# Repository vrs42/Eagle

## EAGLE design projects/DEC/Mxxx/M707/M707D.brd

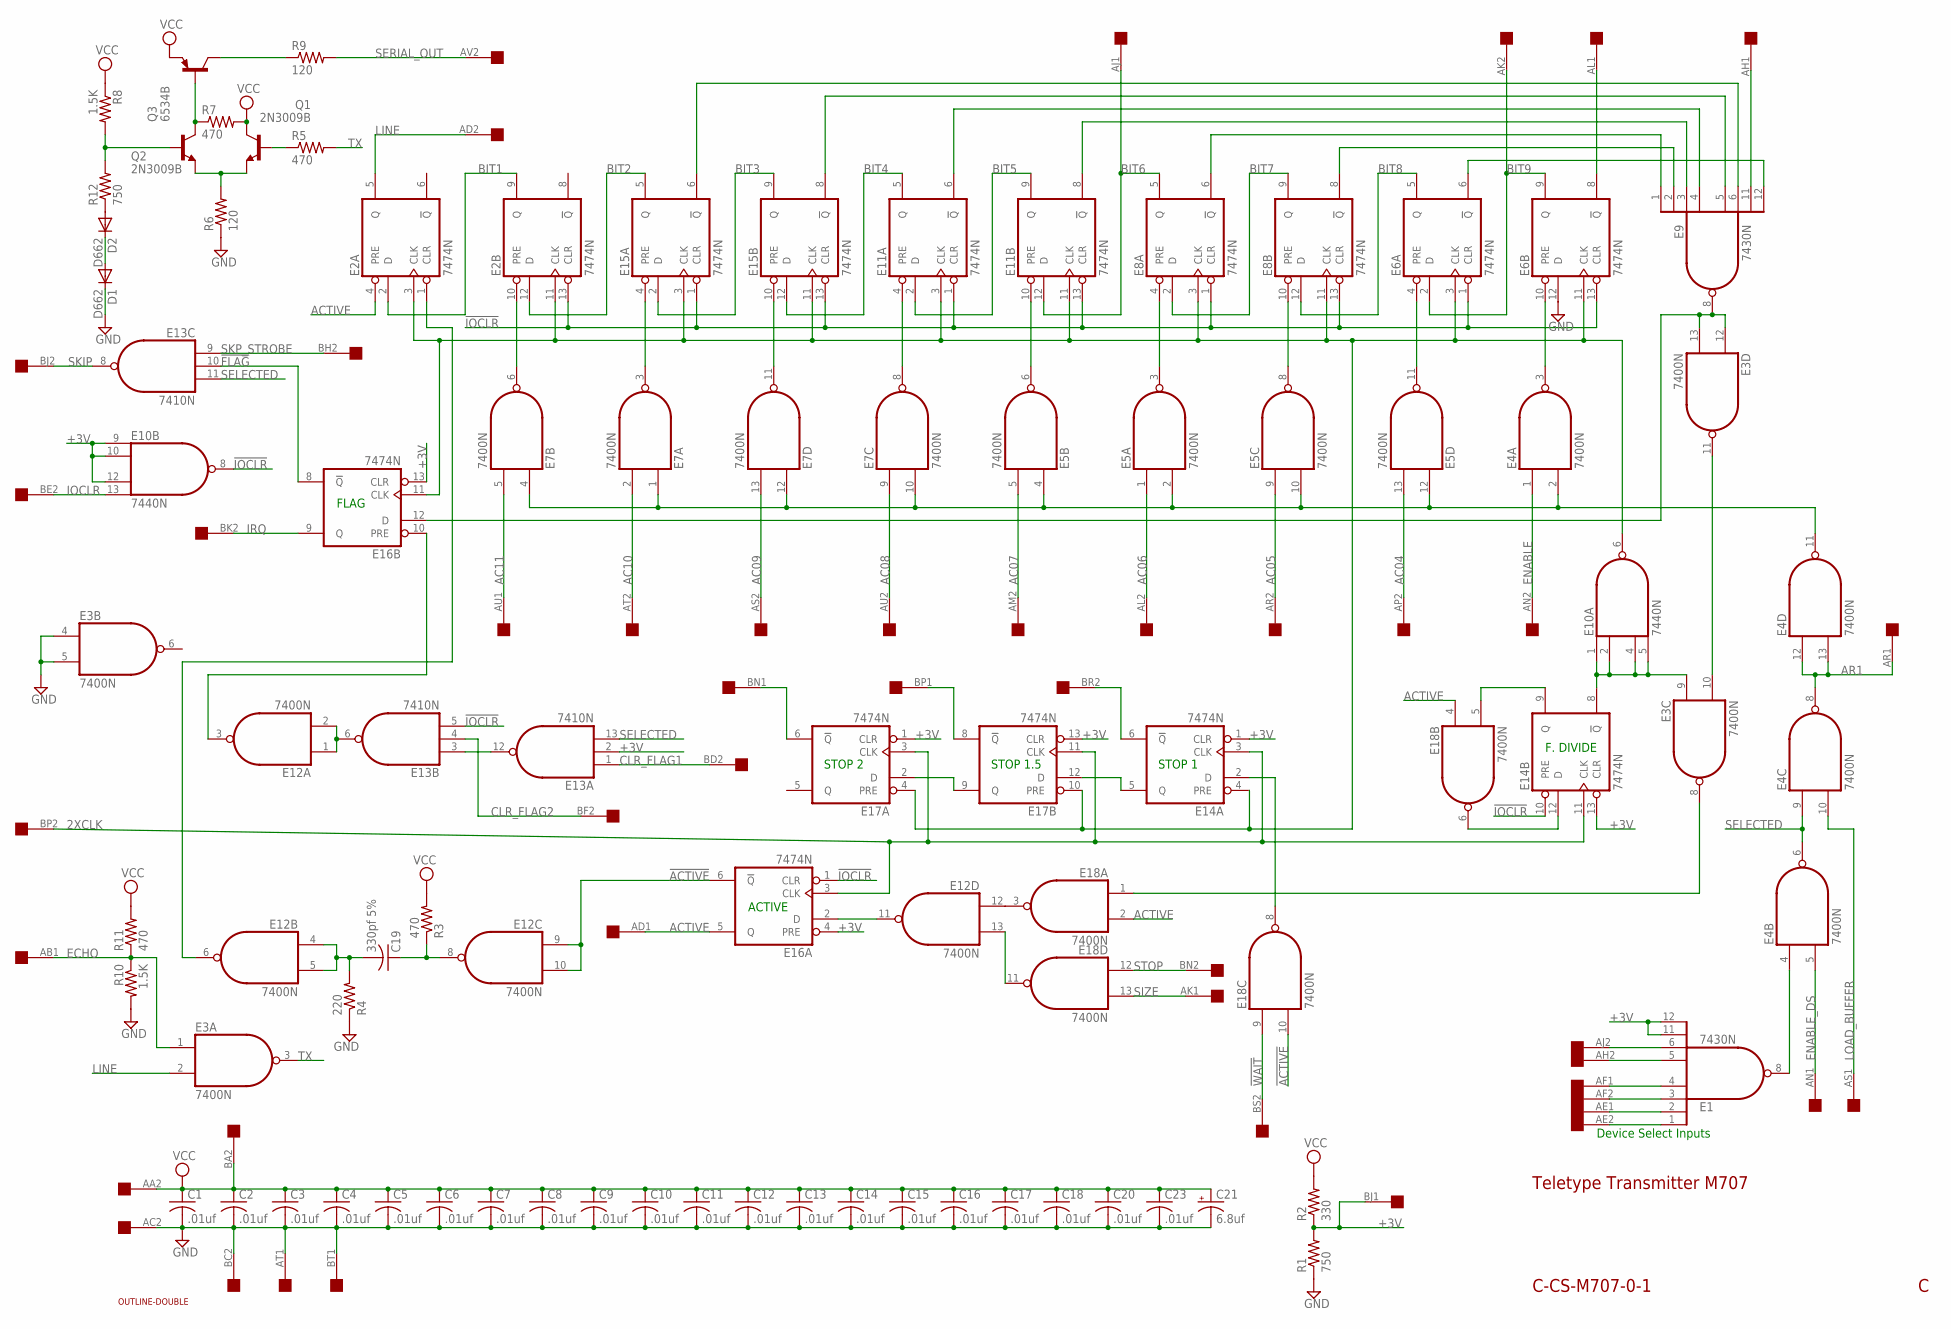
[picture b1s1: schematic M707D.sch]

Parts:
C1, C2, C3, C4, C5, C6, C7, C8, C9, C10, C11, C12, C13, C14, C15, C16, C17, C18, C20, C23: .01uf; C050-025X075
C19: 330pf 5%; C075-032X103
C21: 6.8uf; E15-5
D1, D2: D662; DO35-10
E1, E9: 7430N; DIL14
E2, E6, E8, E11, E14, E15, E16, E17: 7474N; DIL14
E3, E4, E5, E7, E12, E18: 7400N; DIL14
E10: 7440N; DIL14
E13: 7410N; DIL14
Q1, Q2: 2N3009B; TO39
Q3: 6534B; TO39
R1, R12: 750; 0207/10
R2: 330; 0207/10
R3, R5, R7, R11: 470; 0207/10
R4: 220; 0207/10
R6, R9: 120; 0207/10
R8, R10: 1.5K; 0207/10
U$1: OUTLINE-DOUBLE; DOUBLE
U$2: DOUBLE; EDGE-CON4

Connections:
2XCLK: E14.3 (CLK), E14.11 (CLK), E16.3 (CLK), E17.3 (CLK), E17.11 (CLK), U$2.BP2
!ACTIVE: E12.9 (I0), E12.10 (I1), E16.6 (!Q), E18.10 (I1)
!FLAG: E13.10 (I1), E16.8 (!Q)
!IOCLR: E2.13 (CLR), E6.1 (CLR), E6.13 (CLR), E8.1 (CLR), E8.13 (CLR), E10.8 (O), E11.1 (CLR), E11.13 (CLR), E13.5 (I2), E14.10 (PRE), E15.1 (CLR), E15.13 (CLR), E16.1 (CLR)
!WAIT: E18.9 (I0), U$2.BS2
+3V: E1.11 (I6), E1.12 (I7), E10.9 (I0), E10.10 (I1), E10.12 (I2), E13.2 (I1), E14.1 (CLR), E14.13 (CLR), E16.4 (PRE), E16.13 (CLR), E17.1 (CLR), E17.13 (CLR), R1.2, R2.1, U$2.BJ1
AC04: E5.13 (I1), U$2.AP2
AC05: E5.9 (I0), U$2.AR2
AC06: E5.1 (I0), U$2.AL2
AC07: E5.5 (I1), U$2.AM2
AC08: E7.9 (I0), U$2.AU2
AC09: E7.13 (I1), U$2.AS2
AC10: E7.2 (I1), U$2.AT2
AC11: E7.5 (I1), U$2.AU1
ACTIVE: E2.4 (PRE), E16.5 (Q), E18.2 (I1), E18.4 (I0), U$2.AD1
AE1: E1.2 (I1), U$2.AE1
AF1: E1.4 (I3), U$2.AF1
AH1: E9.11 (I6), U$2.AH1
AL1: E6.8 (!Q), U$2.AL1
AR1: E4.8 (O), E4.12 (I0), E4.13 (I1), U$2.AR1
BIT1: E2.2 (D), E2.9 (Q)
BIT2: E2.12 (D), E15.5 (Q)
BIT3: E15.2 (D), E15.9 (Q)
BIT4: E11.5 (Q), E15.12 (D)
BIT5: E11.2 (D), E11.9 (Q)
BIT6: E8.5 (Q), E11.12 (D), U$2.AJ1
BIT7: E8.2 (D), E8.9 (Q)
BIT8: E6.5 (Q), E8.12 (D)
BIT9: E6.2 (D), E6.9 (Q), U$2.AK2
BN1: E17.6 (!Q), U$2.BN1
BP1: E17.8 (!Q), U$2.BP1
CLR_FLAG1: E13.1 (I0), U$2.BD2
CLR_FLAG2: E13.4 (I1), U$2.BF2
ECHO: E3.1 (I0), R10.1, R11.1, U$2.AB1
ENABLE: E4.1 (I0), U$2.AN2
ENABLE_DS: E4.5 (I1), U$2.AN1
GND: C1.2, C2.2, C3.2, C4.2, C5.2, C6.2, C7.2, C8.2, C9.2, C10.2, C11.2, C12.2, C13.2, C14.2, C15.2, C16.2, C17.2, C18.2, C20.2, C21.-, C23.2, D1.C, E1.7 (GND), E2.7 (GND), E3.4 (I0), E3.5 (I1), E3.7 (GND), E4.7 (GND), E5.7 (GND), E6.7 (GND), E6.12 (D), E7.7 (GND), E8.7 (GND), E9.7 (GND), E10.7 (GND), E11.7 (GND), E12.7 (GND), E13.7 (GND), E14.7 (GND), E15.7 (GND), E16.7 (GND), E17.7 (GND), E18.7 (GND), R1.1, R4.1, R6.1, R10.2, U$2.AC2, U$2.AT1, U$2.BC2, U$2.BT1
IOCLR: E10.13 (I3), U$2.BE2
IRQ: E16.9 (Q), U$2.BK2
LINE: E2.5 (Q), E3.2 (I1), U$2.AD2
LOAD_BUFFER: E4.10 (I1), U$2.AS1
unnamed: C19.1, E12.8 (O), R3.1
unnamed: C19.2, E12.4 (I0), E12.5 (I1), R4.2
unnamed: E5.11 (O), E6.4 (PRE)
unnamed: E2.1 (CLR), E12.6 (O)
unnamed: E2.3 (CLK), E2.11 (CLK), E6.3 (CLK), E6.11 (CLK), E8.3 (CLK), E8.11 (CLK), E10.6 (O), E11.3 (CLK), E11.11 (CLK), E14.4 (PRE), E15.3 (CLK), E15.11 (CLK), E16.11 (CLK), E17.4 (PRE), E17.10 (PRE)
unnamed: E3.12 (I0), E3.13 (I1), E9.8 (O), E16.12 (D)
unnamed: E6.6 (!Q), E9.12 (I7)
unnamed: Q3.3 (C), R9.1
unnamed: E1.8 (O), E4.4 (I0)
unnamed: E12.12 (I0), E18.3 (O)
unnamed: E14.12 (D), E18.6 (O)
unnamed: E1.6 (I5), U$2.AJ2
unnamed: E1.5 (I4), U$2.AH2
unnamed: E1.3 (I2), U$2.AF2
unnamed: E14.9 (Q), E18.5 (I1)
unnamed: E1.1 (I0), U$2.AE2
unnamed: E9.6 (I5), E15.6 (!Q)
unnamed: E4.2 (I1), E4.11 (O), E5.2 (I1), E5.4 (I0), E5.10 (I1), E5.12 (I0), E7.1 (I0), E7.4 (I0), E7.10 (I1), E7.12 (I0)
unnamed: E4.3 (O), E6.10 (PRE)
unnamed: D1.A, D2.C
unnamed: D2.A, R12.1
unnamed: Q1.2 (B), R5.1
unnamed: Q2.3 (C), Q3.2 (B), R7.1
unnamed: Q1.1 (E), Q2.1 (E), R6.2
unnamed: E12.11 (O), E16.2 (D)
unnamed: Q2.2 (B), R8.2, R12.2
unnamed: E12.1 (I0), E12.2 (I1), E13.6 (O)
unnamed: E9.5 (I4), E15.8 (!Q)
unnamed: E7.3 (O), E15.4 (PRE)
unnamed: E3.9 (I0), E10.1 (I0), E10.2 (I1), E10.4 (I2), E10.5 (I3), E14.8 (!Q)
unnamed: E3.8 (O), E18.1 (I0)
unnamed: E7.8 (O), E11.4 (PRE)
unnamed: E9.4 (I3), E11.6 (!Q)
unnamed: E7.11 (O), E15.10 (PRE)
unnamed: E5.3 (O), E8.4 (PRE)
unnamed: E2.10 (PRE), E7.6 (O)
unnamed: E12.13 (I1), E18.11 (O)
unnamed: E14.6 (!Q), U$2.BR2
unnamed: E13.3 (I0), E13.12 (O)
unnamed: E17.2 (D), E17.9 (Q)
unnamed: E8.6 (!Q), E9.1 (I0)
unnamed: E8.8 (!Q), E9.2 (I1)
unnamed: E9.3 (I2), E11.8 (!Q)
unnamed: E14.2 (D), E18.8 (O)
unnamed: E14.5 (Q), E17.12 (D)
unnamed: E12.3 (O), E16.10 (PRE)
unnamed: E5.8 (O), E8.10 (PRE)
unnamed: E5.6 (O), E11.10 (PRE)
unnamed: E3.10 (I1), E3.11 (O)
SELECTED: E4.6 (O), E4.9 (I0), E13.11 (I2), E13.13 (I2)
SERIAL_OUT: R9.2, U$2.AV2
SIZE: E18.13 (I1), U$2.AK1
SKIP: E13.8 (O), U$2.BJ2
SKP_STROBE: E13.9 (I0), U$2.BH2
STOP: E18.12 (I0), U$2.BN2
TX: E3.3 (O), R5.2
VCC: C1.1, C2.1, C3.1, C4.1, C5.1, C6.1, C7.1, C8.1, C9.1, C10.1, C11.1, C12.1, C13.1, C14.1, C15.1, C16.1, C17.1, C18.1, C20.1, C21.+, C23.1, E1.14 (VCC), E2.14 (VCC), E3.14 (VCC), E4.14 (VCC), E5.14 (VCC), E6.14 (VCC), E7.14 (VCC), E8.14 (VCC), E9.14 (VCC), E10.14 (VCC), E11.14 (VCC), E12.14 (VCC), E13.14 (VCC), E14.14 (VCC), E15.14 (VCC), E16.14 (VCC), E17.14 (VCC), E18.14 (VCC), Q1.3 (C), Q3.1 (E), R2.2, R3.2, R7.2, R8.1, R11.2, U$2.AA2, U$2.BA2

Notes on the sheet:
C-CS-M707-0-1
Teletype Transmitter M707
Device Select Inputs
F. DIVIDE
FLAG
ACTIVE
STOP 2
STOP 1.5
STOP 1

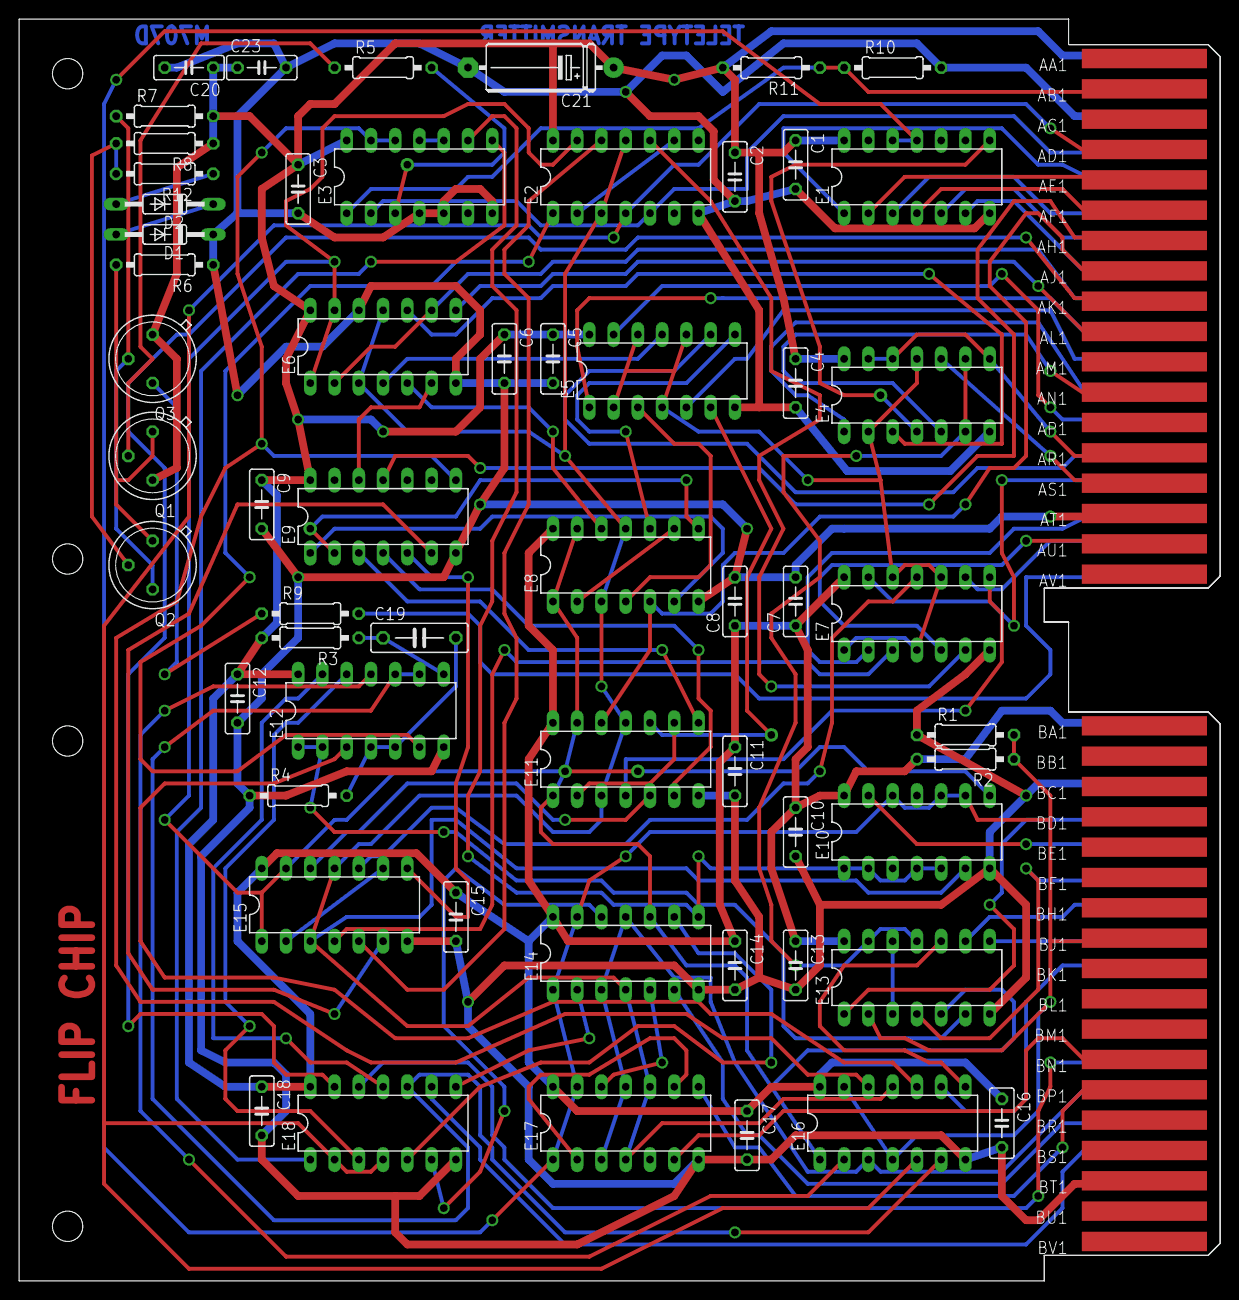
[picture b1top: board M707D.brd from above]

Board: 2 copper layers, 125.7 x 132.1 mm, 59 parts (0 on the bottom side), 98 nets.

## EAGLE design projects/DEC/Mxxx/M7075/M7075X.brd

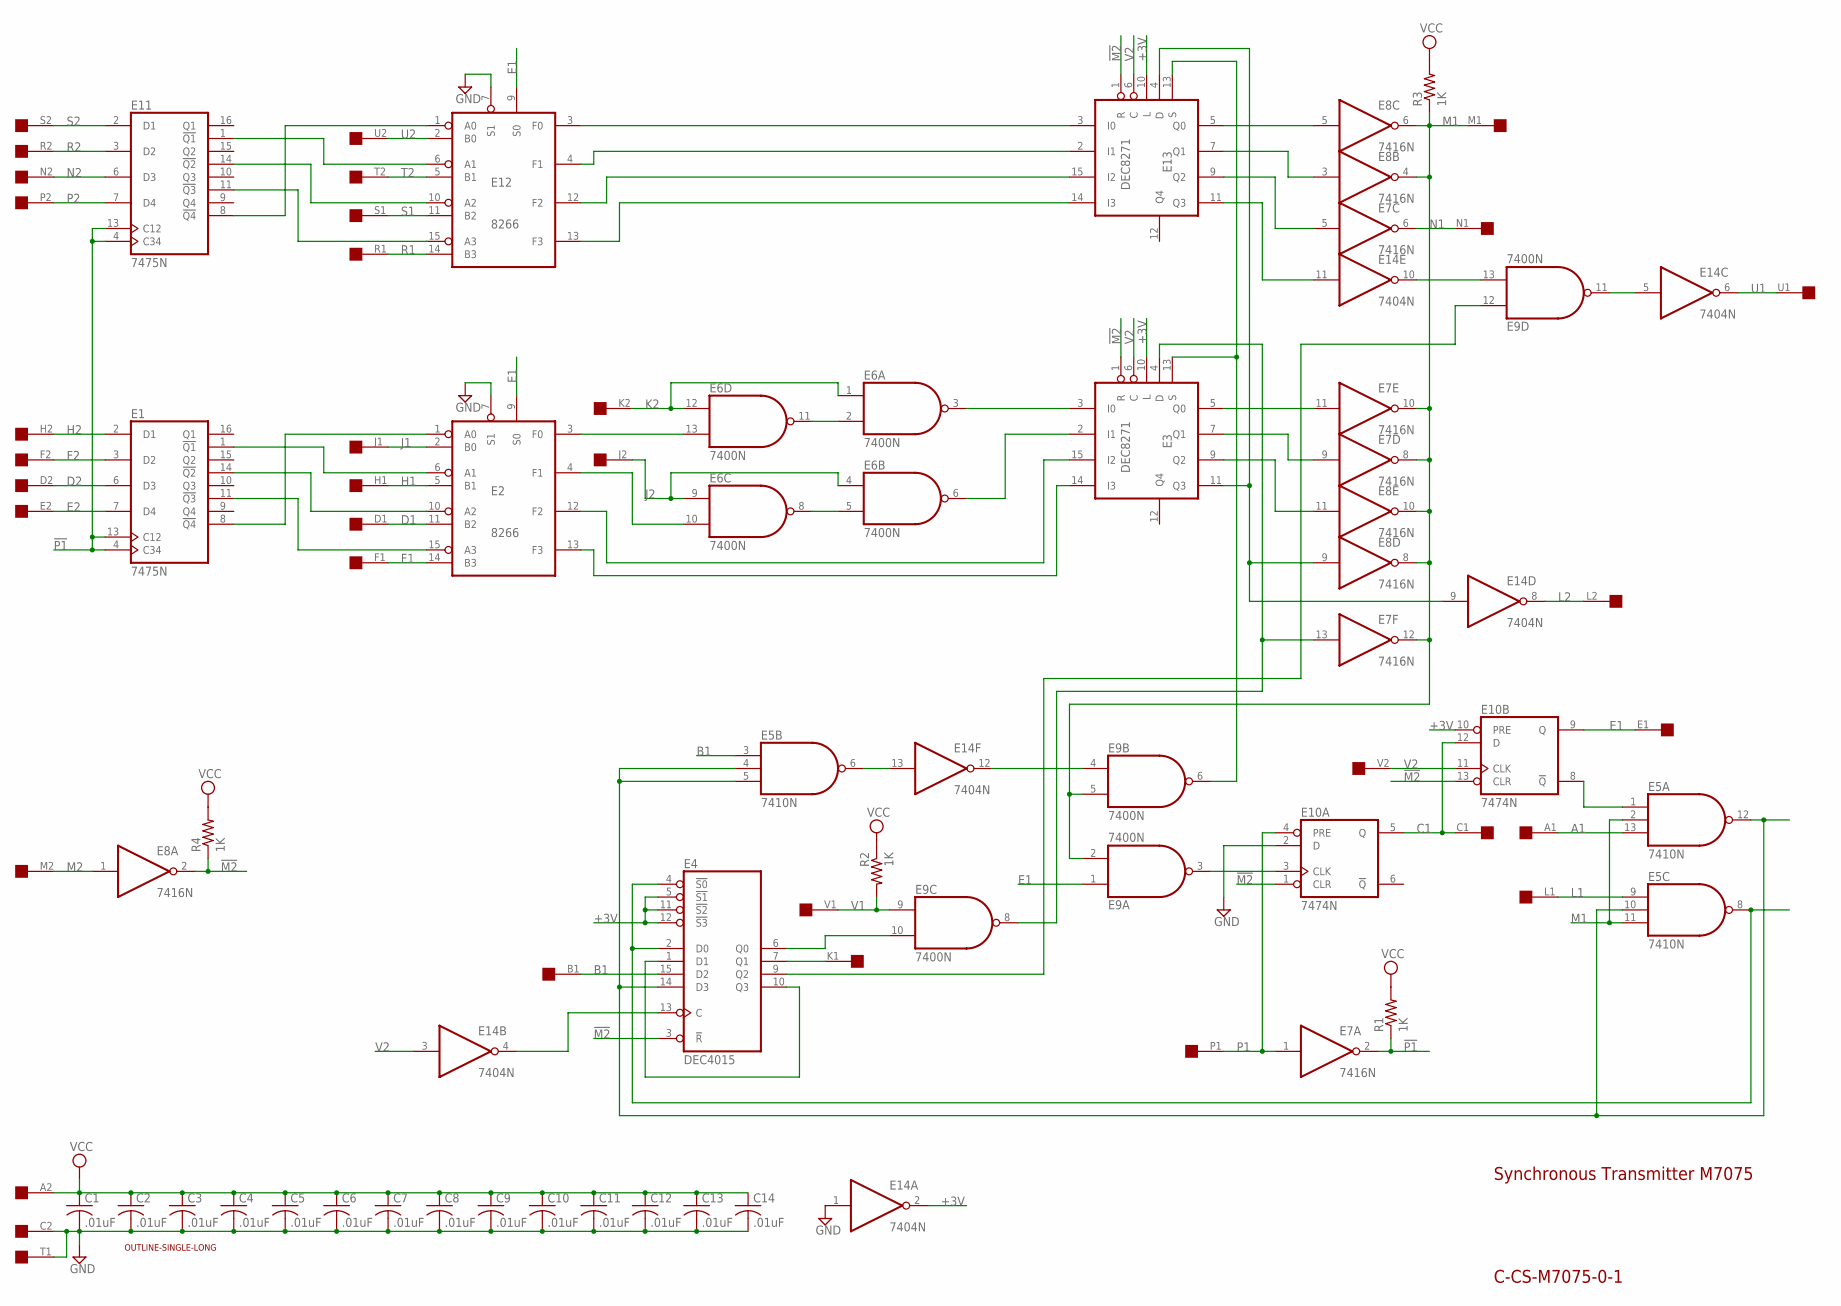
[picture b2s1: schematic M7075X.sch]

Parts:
C1, C2, C3, C4, C5, C6, C7, C8, C9, C10, C11, C12, C13, C14: .01uF; C050-025X075
E1, E11: 7475N; DIL16
E2, E12: 8266; DIL16
E3, E13: DEC8271; DIL16
E4: DEC4015; DIL16
E5: 7410N; DIL14
E6, E9: 7400N; DIL14
E7, E8: 7416N; DIL14
E10: 7474N; DIL14
E14: 7404N; DIL14
R1, R2, R3, R4: 1K; 0207/10
U$1: OUTLINE-SINGLE-LONG; SINGLE-LONG
U$2: SINGLE; EDGE-CON2

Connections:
!M2: E3.1 (R), E4.3 (!R), E8.2 (O), E10.1 (CLR), E10.13 (CLR), E13.1 (R), R4.1
!P1: E1.4 (C34), E1.13 (C12), E7.2 (O), E11.4 (C34), E11.13 (C12), R1.1
+3V: E3.10 (L), E4.5 (!S1), E4.11 (!S2), E4.12 (!S3), E10.10 (PRE), E13.10 (L), E14.2 (O)
A1: E5.13 (I2), U$2.A1
B1: E4.15 (D2), E5.3 (I0), U$2.B1
C1: E10.5 (Q), E10.12 (D), U$2.C1
D1: E2.11 (B2), U$2.D1
D2: E1.6 (D3), U$2.D2
E1: E2.9 (S0), E9.1 (I0), E10.9 (Q), E12.9 (S0), U$2.E1
E2: E1.7 (D4), U$2.E2
F1: E2.14 (B3), U$2.F1
F2: E1.3 (D2), U$2.F2
GND: C1.2, C2.2, C3.2, C4.2, C5.2, C6.2, C7.2, C8.2, C9.2, C10.2, C11.2, C12.2, C13.2, C14.2, E1.12 (GND), E2.7 (S1), E2.8 (GND), E3.8 (GND), E4.8 (GND), E5.7 (GND), E6.7 (GND), E7.7 (GND), E8.7 (GND), E9.7 (GND), E10.2 (D), E10.7 (GND), E11.12 (GND), E12.7 (S1), E12.8 (GND), E13.8 (GND), E14.1 (I), E14.7 (GND), U$2.C2, U$2.T1
H1: E2.5 (B1), U$2.H1
H2: E1.2 (D1), U$2.H2
J1: E2.2 (B0), U$2.J1
J2: E6.4 (I0), E6.9 (I0), U$2.J2
K1: E4.7 (Q1), U$2.K1
K2: E6.1 (I0), E6.12 (I0), U$2.K2
L1: E5.9 (I0), U$2.L1
L2: E14.8 (O), U$2.L2
M1: E5.2 (I1), E5.11 (I2), E7.8 (O), E7.10 (O), E7.12 (O), E8.4 (O), E8.6 (O), E8.8 (O), E8.10 (O), E9.2 (I1), E9.5 (I1), R3.1, U$2.M1
M2: E8.1 (I), U$2.M2
N1: E7.6 (O), U$2.N1
N2: E11.6 (D3), U$2.N2
unnamed: E11.11 (!Q3), E12.15 (A3)
unnamed: E2.3 (F0), E6.13 (I1)
unnamed: E12.3 (F0), E13.3 (I0)
unnamed: E1.11 (!Q3), E2.15 (A3)
unnamed: E1.14 (!Q2), E2.10 (A2)
unnamed: E12.4 (F1), E13.2 (I1)
unnamed: E1.8 (!Q4), E2.1 (A0)
unnamed: E12.13 (F3), E13.14 (I3)
unnamed: E2.4 (F1), E6.10 (I1)
unnamed: E12.12 (F2), E13.15 (I2)
unnamed: E3.9 (Q2), E8.11 (I)
unnamed: E8.5 (I), E13.5 (Q0)
unnamed: E8.3 (I), E13.7 (Q1)
unnamed: E3.11 (Q3), E8.9 (I), E13.4 (D), E14.9 (I)
unnamed: E3.7 (Q1), E7.9 (I)
unnamed: E7.5 (I), E13.9 (Q2)
unnamed: E3.5 (Q0), E7.11 (I)
unnamed: E3.4 (D), E7.13 (I), E9.8 (O)
unnamed: E5.1 (I0), E10.8 (!Q)
unnamed: E9.3 (O), E10.3 (CLK)
unnamed: E3.13 (S), E9.6 (O), E13.13 (S)
unnamed: E9.4 (I0), E14.12 (O)
unnamed: E9.11 (O), E14.5 (I)
unnamed: E9.13 (I1), E14.10 (O)
unnamed: E4.9 (Q2), E9.12 (I0)
unnamed: E4.6 (Q0), E9.10 (I1)
unnamed: E4.14 (D3), E5.4 (I1), E5.5 (I2), E5.10 (I1), E5.12 (O)
unnamed: E4.13 (C), E14.4 (O)
unnamed: E4.1 (D1), E4.10 (Q3)
unnamed: E5.6 (O), E14.13 (I)
unnamed: E13.11 (Q3), E14.11 (I)
unnamed: E4.2 (D0), E4.4 (!S0), E5.8 (O)
unnamed: E11.14 (!Q2), E12.10 (A2)
unnamed: E11.1 (!Q1), E12.6 (A1)
unnamed: E6.5 (I1), E6.8 (O)
unnamed: E6.2 (I1), E6.11 (O)
unnamed: E3.3 (I0), E6.3 (O)
unnamed: E3.2 (I1), E6.6 (O)
unnamed: E2.13 (F3), E3.14 (I3)
unnamed: E2.12 (F2), E3.15 (I2)
P1: E7.1 (I), E10.4 (PRE), U$2.P1
P2: E11.7 (D4), U$2.P2
R1: E12.14 (B3), U$2.R1
R2: E11.3 (D2), U$2.R2
S1: E12.11 (B2), U$2.S1
S2: E11.2 (D1), U$2.S2
S$1: E11.8 (!Q4), E12.1 (A0)
S$4: E1.1 (!Q1), E2.6 (A1)
T2: E12.5 (B1), U$2.T2
U1: E14.6 (O), U$2.U1
U2: E12.2 (B0), U$2.U2
V1: E9.9 (I0), R2.2, U$2.V1
V2: E3.6 (C), E10.11 (CLK), E13.6 (C), E14.3 (I), U$2.V2
VCC: C1.1, C2.1, C3.1, C4.1, C5.1, C6.1, C7.1, C8.1, C9.1, C10.1, C11.1, C12.1, C13.1, C14.1, E1.5 (VCC), E2.16 (VCC), E3.16 (VCC), E4.16 (VCC), E5.14 (VCC), E6.14 (VCC), E7.14 (VCC), E8.14 (VCC), E9.14 (VCC), E10.14 (VCC), E11.5 (VCC), E12.16 (VCC), E13.16 (VCC), E14.14 (VCC), R1.2, R2.1, R3.2, R4.2, U$2.A2

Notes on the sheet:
Synchronous Transmitter M7075
C-CS-M7075-0-1

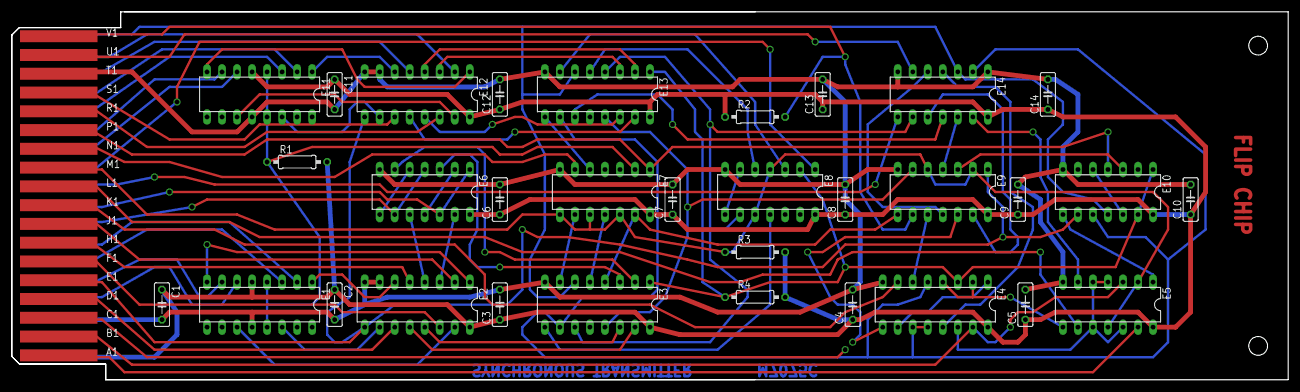
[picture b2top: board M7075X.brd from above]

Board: 3 copper layers, 215.9 x 62.2 mm, 34 parts (0 on the bottom side), 79 nets.

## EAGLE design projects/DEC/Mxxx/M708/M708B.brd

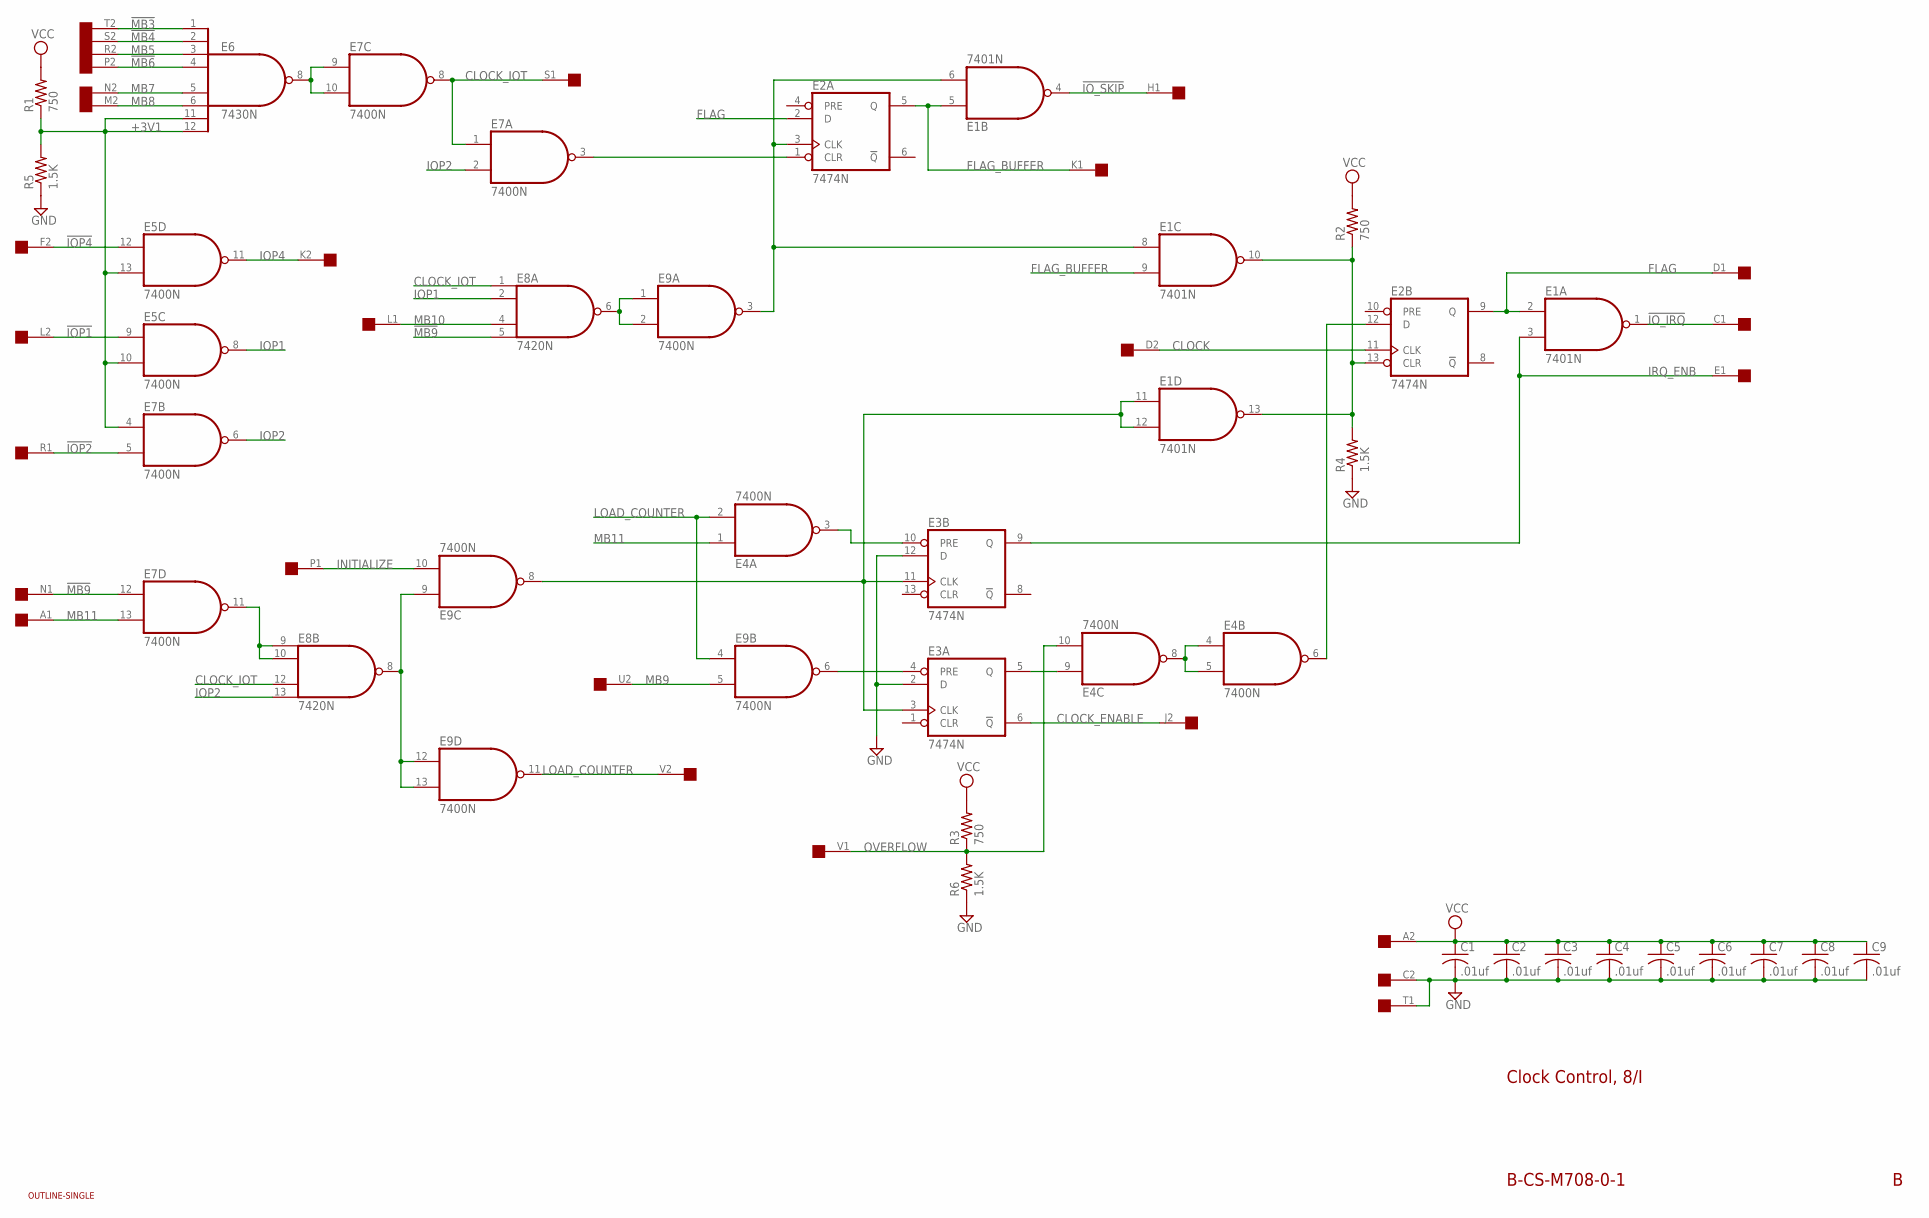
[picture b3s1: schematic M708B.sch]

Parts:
C1, C2, C3, C4, C5, C6, C7, C8, C9: .01uf; C075-032X103
E1: 7401N; DIL14
E2, E3: 7474N; DIL14
E4, E5, E7, E9: 7400N; DIL14
E6: 7430N; DIL14
E8: 7420N; DIL14
R1, R2, R3: 750; 0207/10
R4, R5, R6: 1.5K; 0207/10
U$1: SINGLE; EDGE-CON2
U$4: OUTLINE-SINGLE; SINGLE

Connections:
!CLR_FLAG: E1.10 (O), E1.13 (O), E2.13 (CLR), R2.1, R4.2
!IOP1: E5.9 (I0), U$1.L2
!IOP2: E7.5 (I1), U$1.R1
!IOP4: E5.12 (I0), U$1.F2
!IO_IRQ: E1.1 (O), U$1.C1
!IO_SKIP: E1.4 (O), U$1.H1
!MB3: E6.1 (I0), U$1.T2
!MB4: E6.2 (I1), U$1.S2
!MB6: E6.4 (I3), U$1.P2
!MB9: E7.12 (I0), E8.5 (I3), U$1.N1
+3V1: E5.10 (I1), E5.13 (I1), E6.11 (I6), E6.12 (I7), E7.4 (I0), R1.1, R5.2
CLOCK: E2.11 (CLK), U$1.D2
CLOCK_ENABLE: E3.6 (!Q), U$1.J2
CLOCK_IOT: E7.1 (I0), E7.8 (O), E8.1 (I0), E8.12 (I2), U$1.S1
FLAG: E1.2 (I0), E2.2 (D), E2.9 (Q), U$1.D1
FLAG_BUFFER: E1.5 (I0), E1.9 (I1), E2.5 (Q), U$1.K1
GND: C1.2, C2.2, C3.2, C4.2, C5.2, C6.2, C7.2, C8.2, C9.2, E1.7 (GND), E2.7 (GND), E3.2 (D), E3.7 (GND), E3.12 (D), E4.7 (GND), E5.7 (GND), E6.7 (GND), E7.7 (GND), E8.7 (GND), E9.7 (GND), R4.1, R5.1, R6.1, U$1.C2, U$1.T1
INITIALIZE: E9.10 (I1), U$1.P1
IOP1: E5.8 (O), E8.2 (I1)
IOP2: E7.2 (I1), E7.6 (O), E8.13 (I3)
IOP4: E5.11 (O), U$1.K2
IRQ_ENB: E1.3 (I1), E3.9 (Q), U$1.E1
LOAD_COUNTER: E4.2 (I1), E9.4 (I0), E9.11 (O), U$1.V2
MB5: E6.3 (I2), U$1.R2
MB7: E6.5 (I4), U$1.N2
MB8: E6.6 (I5), U$1.M2
MB9: E9.5 (I1), U$1.U2
MB10: E8.4 (I2), U$1.L1
MB11: E4.1 (I0), E7.13 (I1), U$1.A1
unnamed: E1.11 (I0), E1.12 (I1), E3.3 (CLK), E3.11 (CLK), E9.8 (O)
unnamed: E6.8 (O), E7.9 (I0), E7.10 (I1)
unnamed: E2.1 (CLR), E7.3 (O)
unnamed: E8.6 (O), E9.1 (I0), E9.2 (I1)
unnamed: E1.6 (I1), E1.8 (I0), E2.3 (CLK), E9.3 (O)
unnamed: E7.11 (O), E8.9 (I0), E8.10 (I1)
unnamed: E8.8 (O), E9.9 (I0), E9.12 (I0), E9.13 (I1)
unnamed: E3.5 (Q), E4.9 (I0)
unnamed: E3.4 (PRE), E9.6 (O)
unnamed: E3.10 (PRE), E4.3 (O)
unnamed: E4.4 (I0), E4.5 (I1), E4.8 (O)
unnamed: E2.12 (D), E4.6 (O)
OVERFLOW: E4.10 (I1), R3.1, R6.2, U$1.V1
VCC: C1.1, C2.1, C3.1, C4.1, C5.1, C6.1, C7.1, C8.1, C9.1, E1.14 (VCC), E2.14 (VCC), E3.14 (VCC), E4.14 (VCC), E5.14 (VCC), E6.14 (VCC), E7.14 (VCC), E8.14 (VCC), E9.14 (VCC), R1.2, R2.2, R3.2, U$1.A2

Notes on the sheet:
Clock Control, 8/I
B-CS-M708-0-1

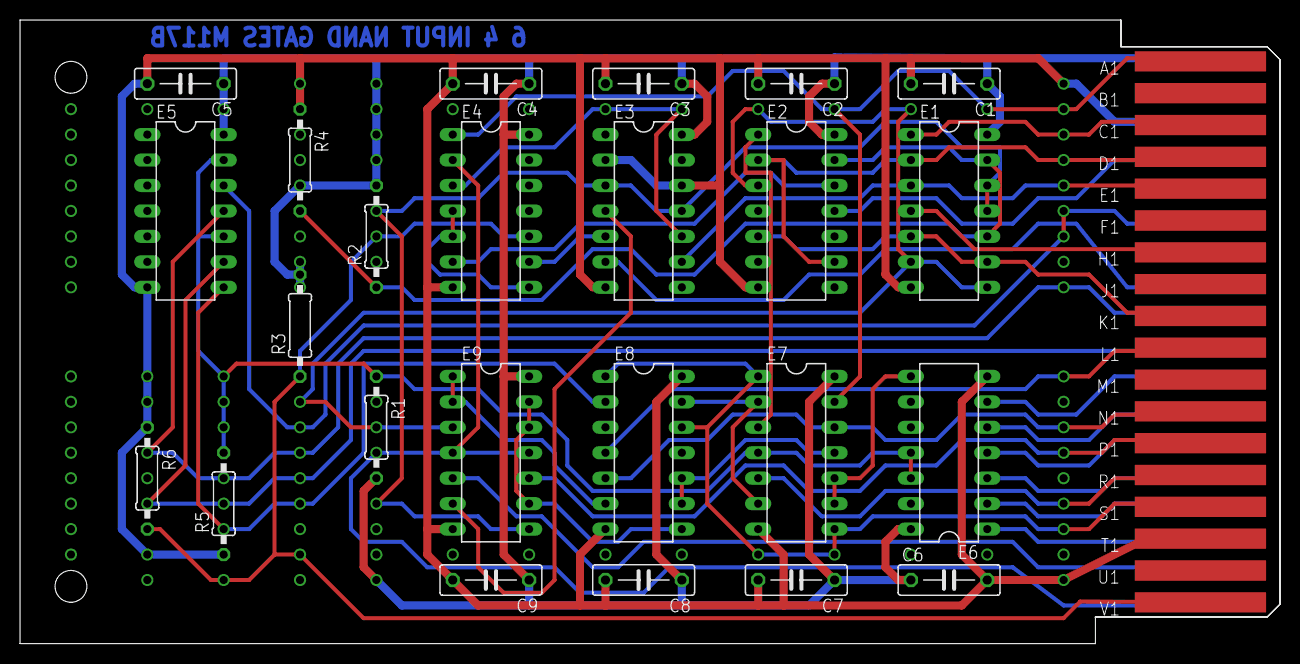
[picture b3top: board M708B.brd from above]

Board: 2 copper layers, 125.7 x 62.2 mm, 26 parts (0 on the bottom side), 43 nets.
